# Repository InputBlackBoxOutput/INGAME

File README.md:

# INGAME

INGAME is a motion emulator with virtual reality features for playing first person
shooting/adventure games. Virtual reality (VR) is a simulated experience that can be similar to
or completely different from the real world. INGAME has been designed to provide the user
with the feeling of being 'IN-the-GAME'. INGAME is modular in nature and consists of the
following modules.

1. HID module
1. Controller module
1. Pedometer module
1. VR headset

The first three modules listed above have been explained in detail later in the document. The
VR headset provides split stereo video to the user. The following image shows the functional
block diagram of the INGAME system 

## Salient features
* Modular to support addons
* Tangle free gaming since the entire system is wireless
* Adaptable to any first person shooting/adventure game
* Minimal lag during gaming due to high-speed data transfer
* Power saving mode to make the battery last longer
* Product certifications: CE certified and ROHS compliant 

## HID module 

### Functions 
- Act as a wireless gateway between the modules worn by the user and the computer
- Connect with the computer via USB as an HID device
- Receive data wirelessly and then map the data to controls of the selected game and send appropriate key strokes to the computer
- Switch the game controls mapping depending on the user selected game
- Display a menu showing information about the system

## Controller module

### Functions
- Connect with the HID module wirelessly
- Send data associated with a button when a button is pressed
- Read IMU data, compute equivalent mouse movement and send the data to the HID module
- Calibrate the IMU device when the calibration button is pressed
- Monitor battery level and sound a buzzer when the battery is low
- Switch to power saving mode upon user inactivity
- [Optional] Control a vibration motor to simulate gunfire which increases in intensity per trigger button press

## Pedometer module

### Functions
- Connect with the HID module wirelessly
- Read accelerometer data, detect steps and send the data to the HID module
- Calibrate the IMU device when the calibration button is pressed
- Monitor battery level and sound a buzzer when the battery is low
- Switch to power saving mode upon user inactivity

## VR Headset
### Frame
|\#|Source|
|--|--|
|1|https://www.alibaba.com/product-detail/Vr-Helmet-SC-G07E-9-0_1600236677589.html|
||https://www.alibaba.com/product-detail/VR-G02ED-headset-version-Blu-ray_1600236686455.html|

### Display
|\#|Source|
|--|--|
|1|https://www.aliexpress.us/item/3256804913653723.html|
|2|https://www.alibaba.com/product-detail/Tft-Display-Driver-Board-VR-Headset_60669018564.html|

### Made with lots of ⏱️, 📚 and ☕ by InputBlackBoxOutput

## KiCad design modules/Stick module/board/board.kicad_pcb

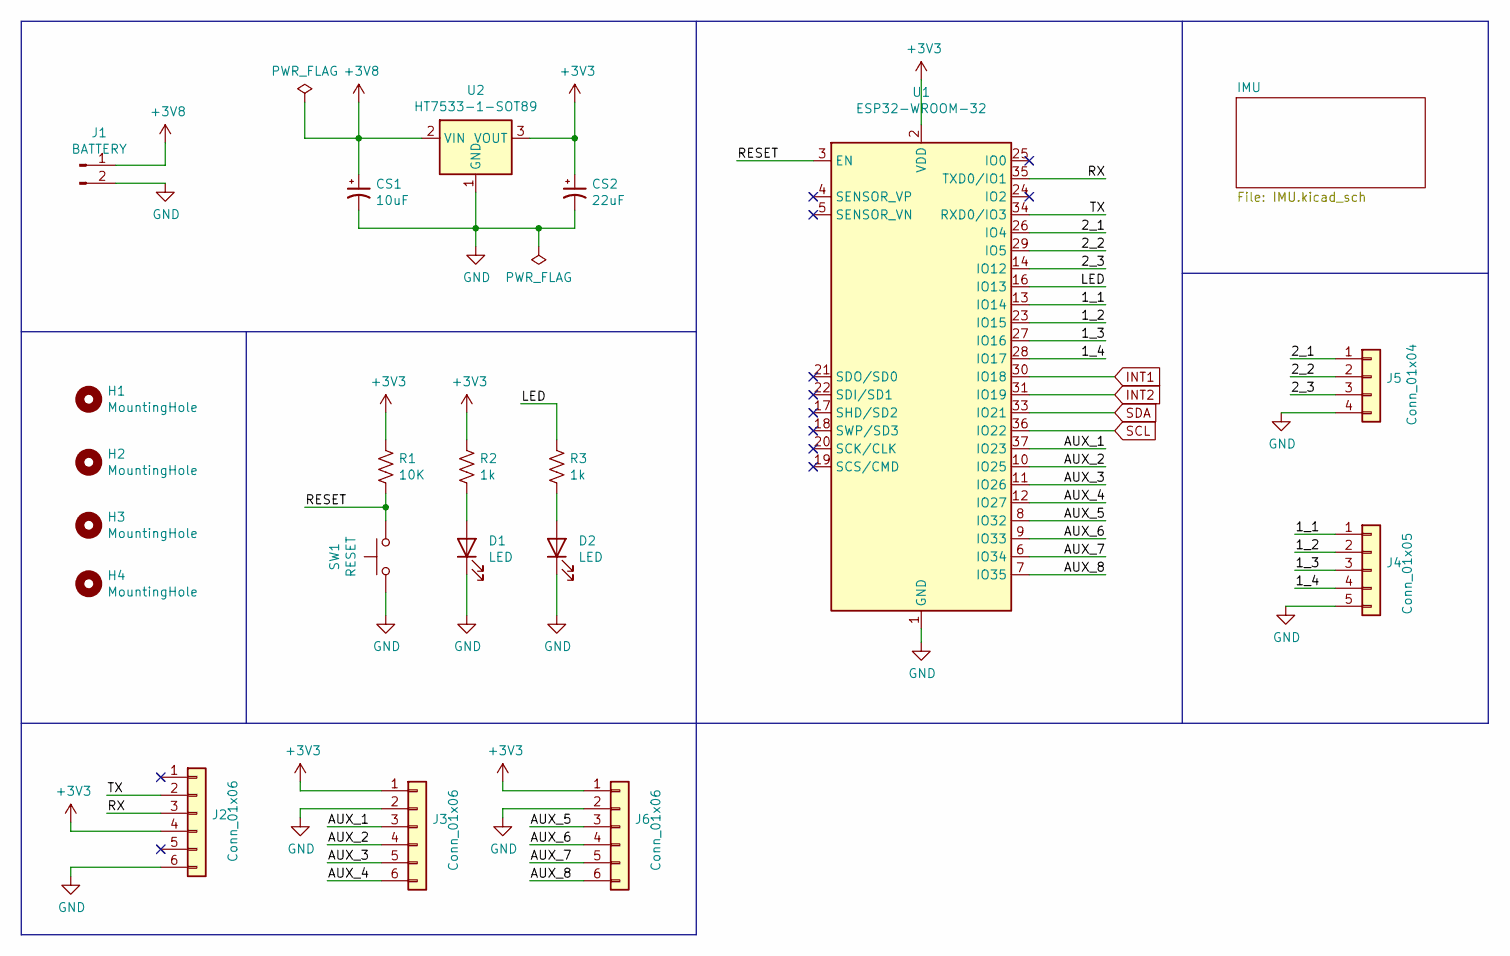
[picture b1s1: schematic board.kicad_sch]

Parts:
CS1: 10uF; C_0805_2012Metric_Pad1.18x1.45mm_HandSolder
CS2: 22uF; C_0805_2012Metric_Pad1.18x1.45mm_HandSolder
D1, D2: LED; LED_0805_2012Metric_Pad1.15x1.40mm_HandSolder
H1, H2, H3, H4: MountingHole; MountingHole_2.2mm_M2
J1: BATTERY; SolderWire_1x02_P2.00mm
J2, J3, J6: Conn_01x06; SolderWire_1x06_P2.54mm
J4: Conn_01x05; SolderWire_1x05_P2.54mm
J5: Conn_01x04; SolderWire_1x04_P2.54mm
R1: 10K; R_0805_2012Metric_Pad1.20x1.40mm_HandSolder
R2, R3: 1k; R_0805_2012Metric_Pad1.20x1.40mm_HandSolder
SW1: RESET; SW_SPST_B3U-1000P
U1: ESP32-WROOM-32
U2: HT7533-1-SOT89; SOT-89-3

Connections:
+3V3: CS2.1, J2.4, J3.1, J6.1, R1.1, R2.1, U1.2 (VDD), U2.3 (VOUT); also elsewhere on the board
+3V8: CS1.1, J1.1, U2.2 (VIN)
/1_1: J4.1, U1.13 (IO14)
/1_2: J4.2, U1.23 (IO15)
/1_3: J4.3, U1.27 (IO16)
/1_4: J4.4, U1.28 (IO17)
/2_1: J5.1, U1.26 (IO4)
/2_2: J5.2, U1.29 (IO5)
/2_3: J5.3, U1.14 (IO12)
/AUX_1: J3.3, U1.37 (IO23)
/AUX_2: J3.4, U1.10 (IO25)
/AUX_3: J3.5, U1.11 (IO26)
/AUX_4: J3.6, U1.12 (IO27)
/AUX_5: J6.3, U1.8 (IO32)
/AUX_6: J6.4, U1.9 (IO33)
/AUX_7: J6.5, U1.6 (IO34)
/AUX_8: J6.6, U1.7 (IO35)
/LED: R3.1, U1.16 (IO13)
/RESET: R1.2, SW1.2, U1.3 (EN)
/RX: J2.3, U1.35 (TXD0/IO1)
/TX: J2.2, U1.34 (RXD0/IO3)
GND: CS1.2, CS2.2, D1.1 (K), D2.1 (K), J1.2, J2.6, J3.2, J4.5, J5.4, J6.2, SW1.1, U1.1 (GND), U1.15 (GND), U1.38 (GND), U1.39 (GND), U2.1 (GND); also elsewhere on the board
INT1: U1.30 (IO18); also elsewhere on the board
INT2: U1.31 (IO19); also elsewhere on the board
unnamed: D1.2 (A), R2.2
unnamed: D2.2 (A), R3.2
SCL: U1.36 (IO22); also elsewhere on the board
SDA: U1.33 (IO21); also elsewhere on the board

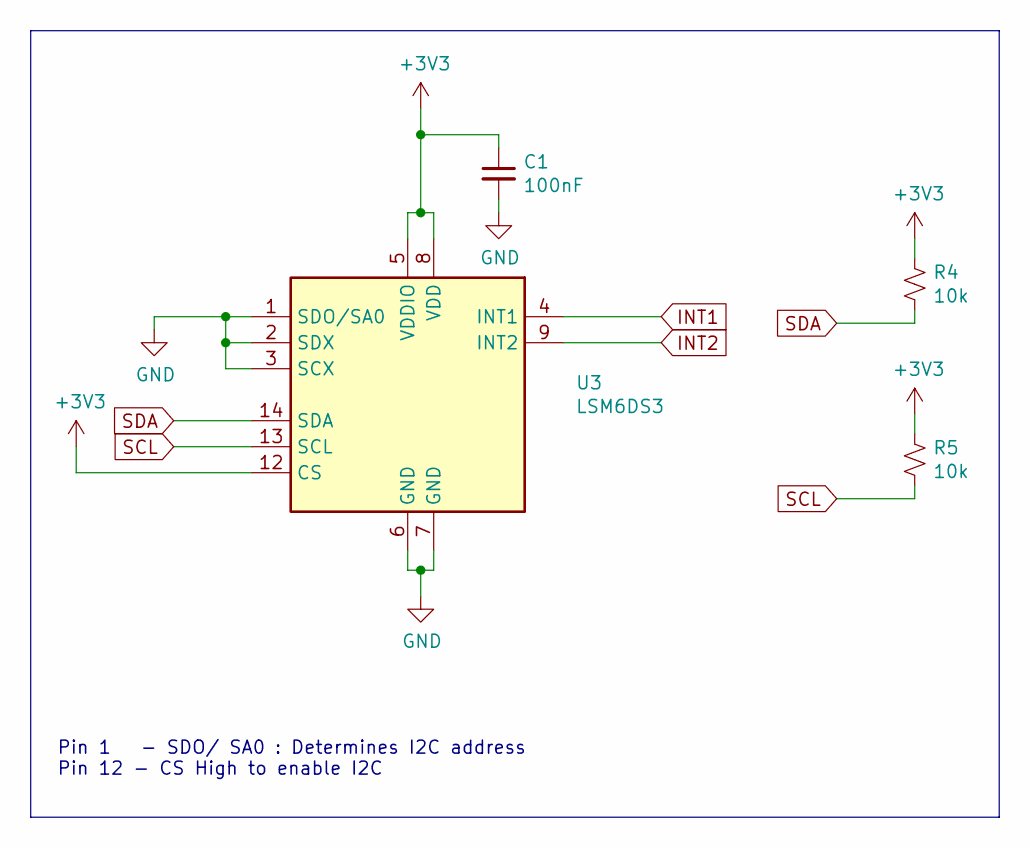
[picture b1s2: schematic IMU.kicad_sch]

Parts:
C1: 100nF; C_0805_2012Metric_Pad1.18x1.45mm_HandSolder
R4, R5: 10k; R_0805_2012Metric_Pad1.20x1.40mm_HandSolder
U3: LSM6DS3; LGA-14_3x2.5mm_P0.5mm_LayoutBorder3x4y

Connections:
+3V3: C1.1, R4.1, R5.1, U3.5 (VDDIO), U3.8 (VDD), U3.12 (CS); also elsewhere on the board
GND: C1.2, U3.1 (SDO/SA0), U3.2 (SDX), U3.3 (SCX), U3.6 (GND), U3.7 (GND); also elsewhere on the board
INT1: U3.4 (INT1); also elsewhere on the board
INT2: U3.9 (INT2); also elsewhere on the board
SCL: R5.2, U3.13 (SCL); also elsewhere on the board
SDA: R4.2, U3.14 (SDA); also elsewhere on the board

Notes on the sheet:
Pin 1 - SDO/ SA0 : Determines I2C address Pin 12 - CS High to enable I2C

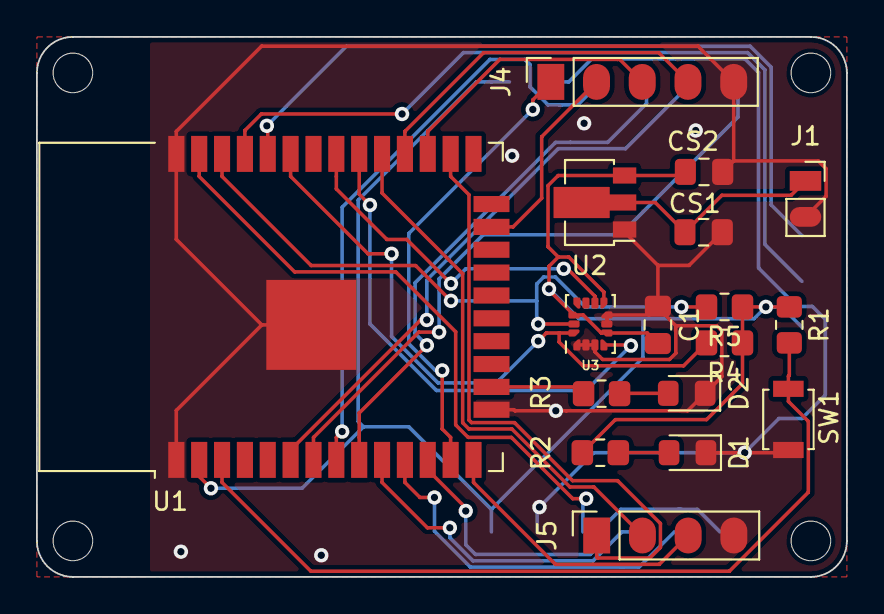
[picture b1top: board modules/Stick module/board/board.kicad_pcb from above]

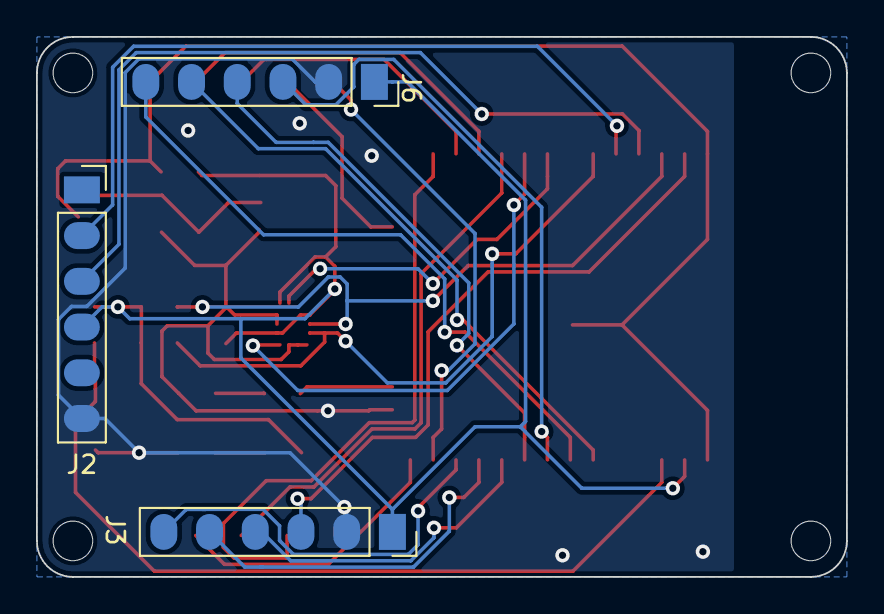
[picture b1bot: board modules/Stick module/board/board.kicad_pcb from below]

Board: 2 copper layers, 45.0 x 30.0 mm, 24 parts (3 on the bottom side), 28 nets.

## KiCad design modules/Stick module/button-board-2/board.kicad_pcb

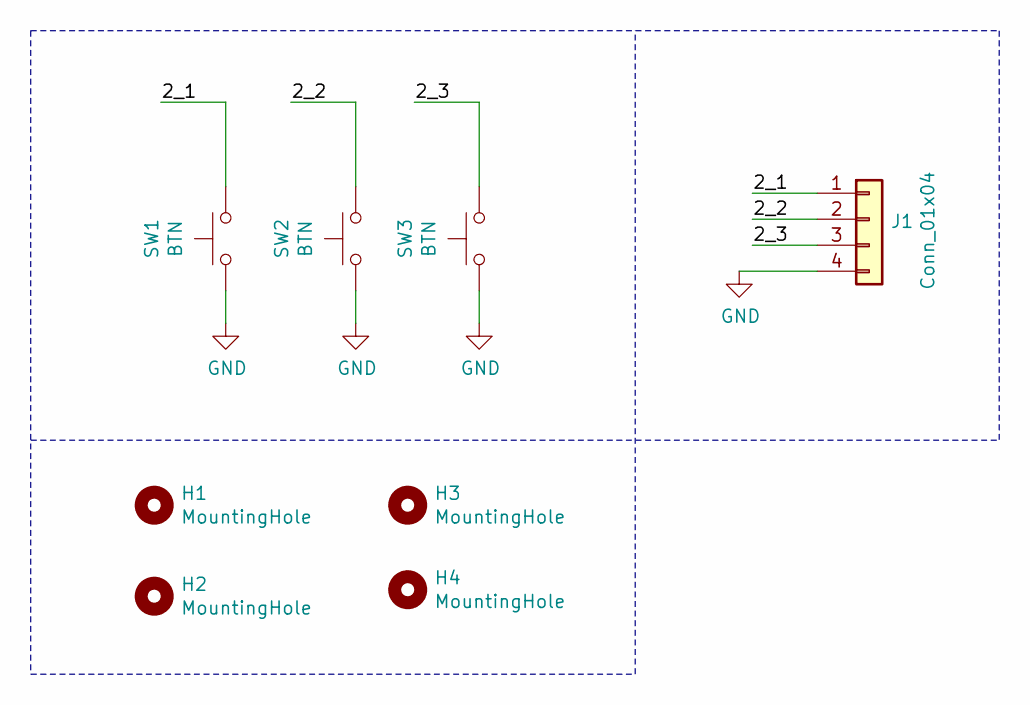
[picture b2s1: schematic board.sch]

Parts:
H1, H2, H3, H4: MountingHole; MountingHole_2.2mm_M2
J1: Conn_01x04; SolderWire_1x04_P2.54mm
SW1, SW2, SW3: BTN; SW_SPST_Omron_B3FS-100xP

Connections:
/2_1: J1.1, SW1.2
/2_2: J1.2, SW2.2
/2_3: J1.3, SW3.2
GND: J1.4, SW1.1, SW2.1, SW3.1

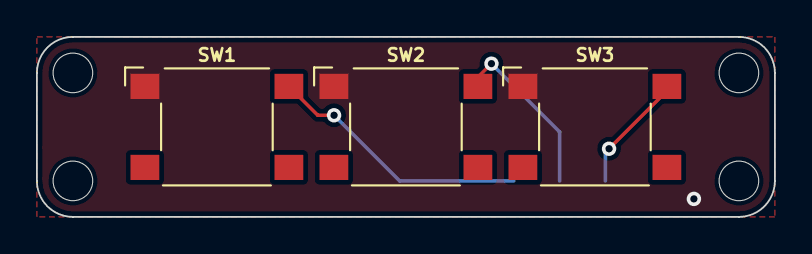
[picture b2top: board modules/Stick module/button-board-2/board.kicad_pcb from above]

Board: 2 copper layers, 41.0 x 10.0 mm, 8 parts (1 on the bottom side), 4 nets.

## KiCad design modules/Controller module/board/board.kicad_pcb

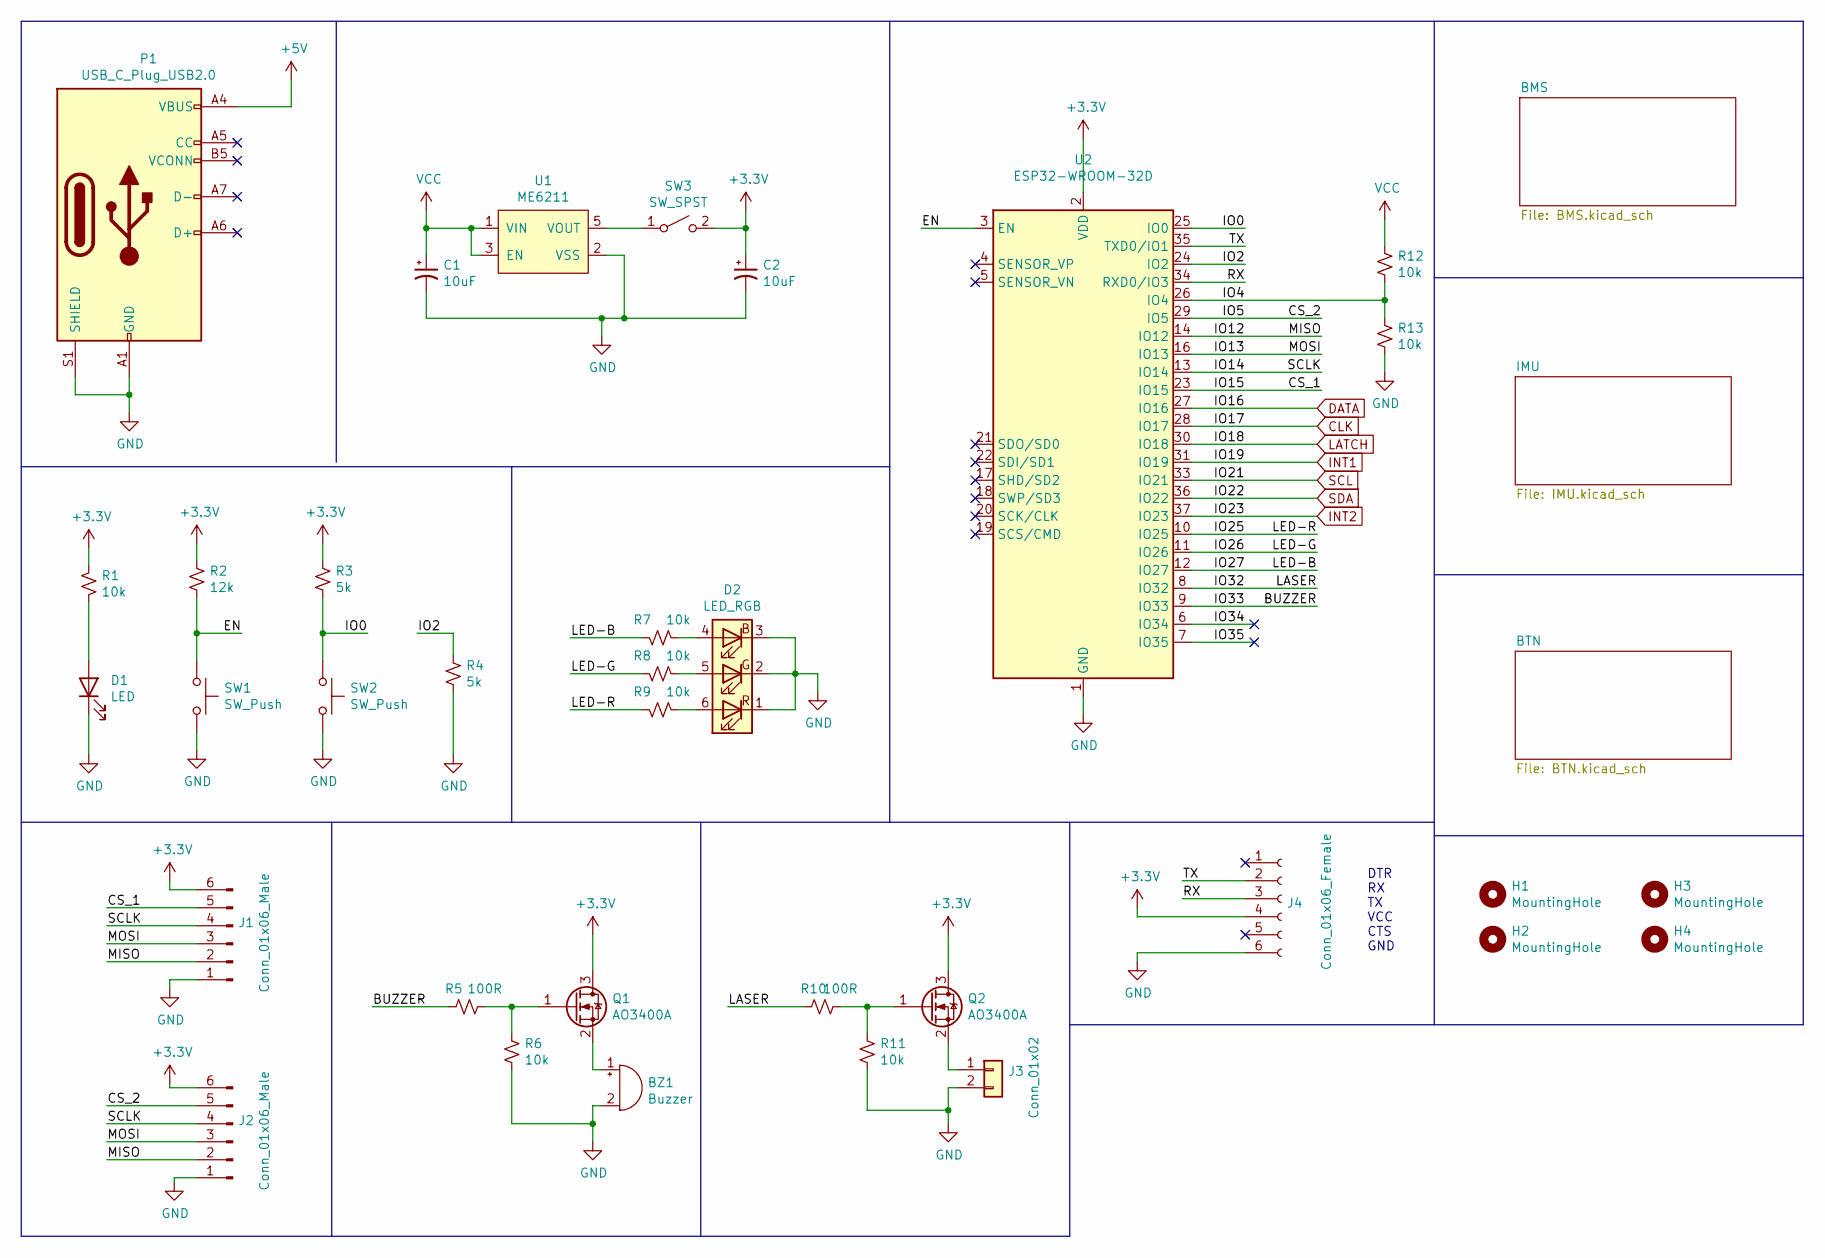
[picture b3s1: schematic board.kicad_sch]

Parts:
BZ1: Buzzer; Buzzer_Murata_PKMCS0909E4000-R1
C1, C2: 10uF; C_0805_2012Metric_Pad1.18x1.45mm_HandSolder
D1: LED; LED_0805_2012Metric_Pad1.15x1.40mm_HandSolder
D2: LED_RGB; LED_RGB_5050-6
H1, H2, H3, H4: MountingHole; MountingHole_2.2mm_M2
J1, J2: Conn_01x06_Male; SolderWire_1x06_P2.54mm
J3: Conn_01x02; SolderWire_1x02_P2.00mm
J4: Conn_01x06_Female; SolderWire_1x06_P2.54mm
P1: USB_C_Plug_USB2.0; GCT_USB4151-GF-C_REVA
Q1, Q2: AO3400A; SOT-23
R1, R6, R7, R8, R9, R11, R12, R13: 10k; R_0805_2012Metric_Pad1.20x1.40mm_HandSolder
R2: 12k; R_0805_2012Metric_Pad1.20x1.40mm_HandSolder
R3, R4: 5k; R_0805_2012Metric_Pad1.20x1.40mm_HandSolder
R5, R10: 100R; R_0805_2012Metric_Pad1.20x1.40mm_HandSolder
SW1, SW2: SW_Push; SW_SPST_B3U-1000P
SW3: SW_SPST; SolderWire_1x02_P2.00mm
U1: ME6211; SOT-23-5_HandSoldering
U2: ESP32-WROOM-32D; ESP32-WROOM-32

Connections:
+5V: P1.A4 (VBUS), P1.A9 (VBUS), P1.B4 (VBUS), P1.B9 (VBUS); also elsewhere on the board
/BUZZER: R5.2, U2.9 (IO33)
/CS_1: J1.5, U2.23 (IO15)
/CS_2: J2.5, U2.29 (IO5)
/EN: R2.2, SW1.1, U2.3 (EN)
/IO0: R3.2, SW2.1, U2.25 (IO0)
/IO2: R4.1, U2.24 (IO2)
/IO4: R12.2, R13.1, U2.26 (IO4)
/IO12: J1.2, J2.2, U2.14 (IO12)
/IO13: J1.3, J2.3, U2.16 (IO13)
/IO14: J1.4, J2.4, U2.13 (IO14)
/IO25: R9.1, U2.10 (IO25)
/IO26: R8.1, U2.11 (IO26)
/IO27: R7.1, U2.12 (IO27)
/IO32: R10.2, U2.8 (IO32)
/RX: J4.3, U2.34 (RXD0/IO3)
/TX: J4.2, U2.35 (TXD0/IO1)
CLK: U2.28 (IO17); also elsewhere on the board
DATA: U2.27 (IO16); also elsewhere on the board
GND: BZ1.2 (+), C1.2, C2.2, D1.1 (K), D2.1 (RK), D2.2 (GK), D2.3 (BK), J1.1, J2.1, J3.2, J4.6, P1.A1 (GND), P1.A12 (GND), P1.B1 (GND), P1.B12 (GND), P1.S1 (SHIELD), R4.2, R6.2, R11.2, R13.2, SW1.2, SW2.2, U1.2 (VSS), U2.1 (GND), U2.15 (GND), U2.38 (GND), U2.39 (GND); also elsewhere on the board
INT1: U2.31 (IO19); also elsewhere on the board
INT2: U2.37 (IO23); also elsewhere on the board
LATCH: U2.30 (IO18); also elsewhere on the board
unnamed: BZ1.1 (-), Q1.2 (S)
unnamed: D1.2 (A), R1.2
unnamed: D2.4 (BA), R7.2
unnamed: D2.5 (GA), R8.2
unnamed: D2.6 (RA), R9.2
unnamed: J3.1, Q2.2 (S)
unnamed: Q1.1 (G), R5.1, R6.1
unnamed: Q2.1 (G), R10.1, R11.1
unnamed: SW3.1 (A), U1.5 (VOUT)
SCL: U2.33 (IO21); also elsewhere on the board
SDA: U2.36 (IO22); also elsewhere on the board
VCC: C1.1, R12.1, U1.1 (VIN), U1.3 (EN); also elsewhere on the board

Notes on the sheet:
DTR RX TX VCC CTS GND

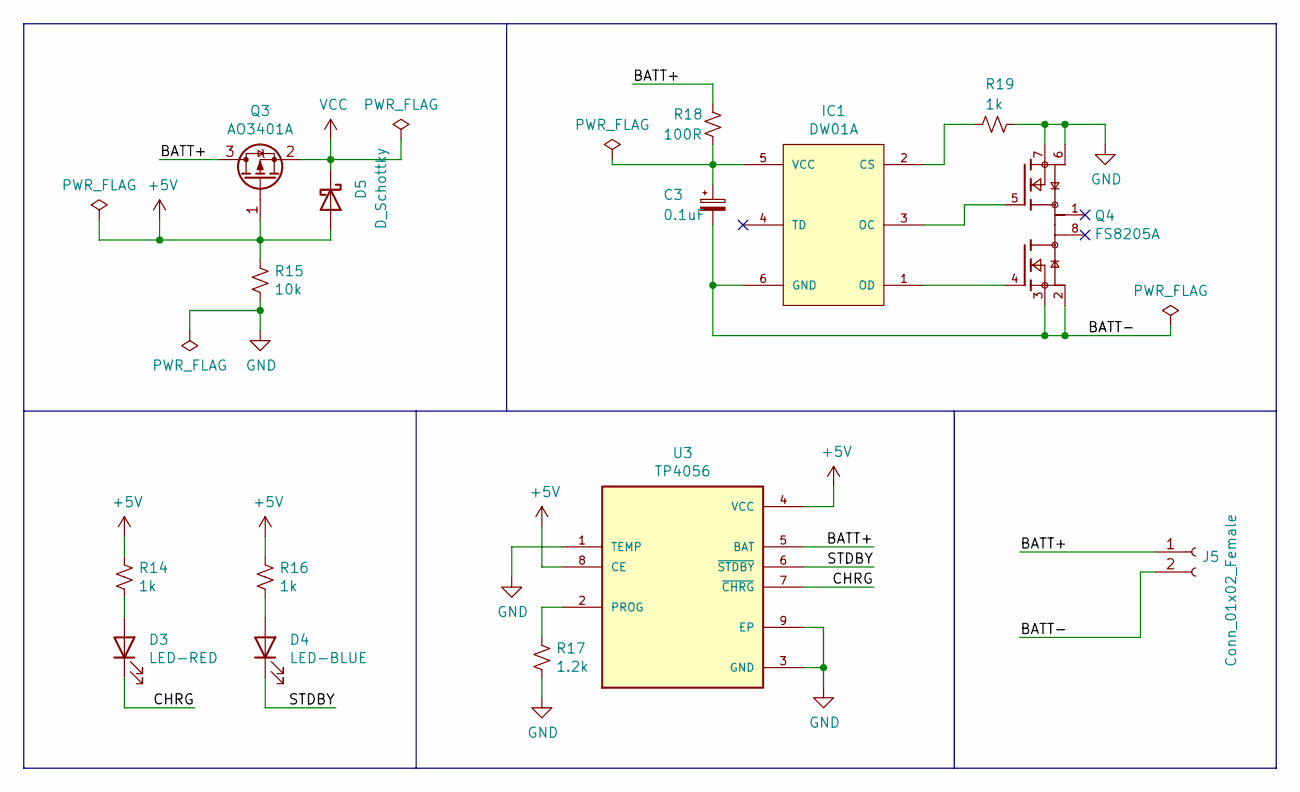
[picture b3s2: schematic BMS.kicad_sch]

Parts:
C3: 0.1uF; C_0805_2012Metric_Pad1.18x1.45mm_HandSolder
D3: LED-RED; LED_0805_2012Metric_Pad1.15x1.40mm_HandSolder
D4: LED-BLUE; LED_0805_2012Metric_Pad1.15x1.40mm_HandSolder
D5: D_Schottky; D_SMA
IC1: DW01A; SOT-23-6_Handsoldering; MPN DW01A; LCSC C351410
J5: Conn_01x02_Female; SolderWire_1x02_P2.00mm
Q3: AO3401A; SOT-23
Q4: FS8205A; SOP65P640X120-8N; PARTREV 1.7
R14, R16, R19: 1k; R_0805_2012Metric_Pad1.20x1.40mm_HandSolder
R15: 10k; R_0805_2012Metric_Pad1.20x1.40mm_HandSolder
R17: 1.2k; R_0805_2012Metric_Pad1.20x1.40mm_HandSolder
R18: 100R; R_0805_2012Metric_Pad1.20x1.40mm_HandSolder
U3: TP4056; SOP127P600X175-9N

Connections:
+5V: D5.2 (A), Q3.1 (G), R14.1, R15.1, R16.1, U3.4 (VCC), U3.8 (CE); also elsewhere on the board
/BMS/BATT+: J5.1, Q3.3 (D), R18.1, U3.5 (BAT)
/BMS/BATT-: C3.2, IC1.6 (GND), J5.2, Q4.2, Q4.3
/BMS/CHRG: D3.1 (K), U3.7 (~CHRG)
/BMS/STDBY: D4.1 (K), U3.6 (~STDBY)
GND: Q4.6, Q4.7, R15.2, R17.2, R19.1, U3.1 (TEMP), U3.3 (GND), U3.9 (EP); also elsewhere on the board
unnamed: C3.1, IC1.5 (VCC), R18.2
unnamed: D3.2 (A), R14.2
unnamed: D4.2 (A), R16.2
unnamed: IC1.1 (OD), Q4.4
unnamed: IC1.2 (CS), R19.2
unnamed: IC1.3 (OC), Q4.5
unnamed: R17.1, U3.2 (PROG)
VCC: D5.1 (K), Q3.2 (S); also elsewhere on the board

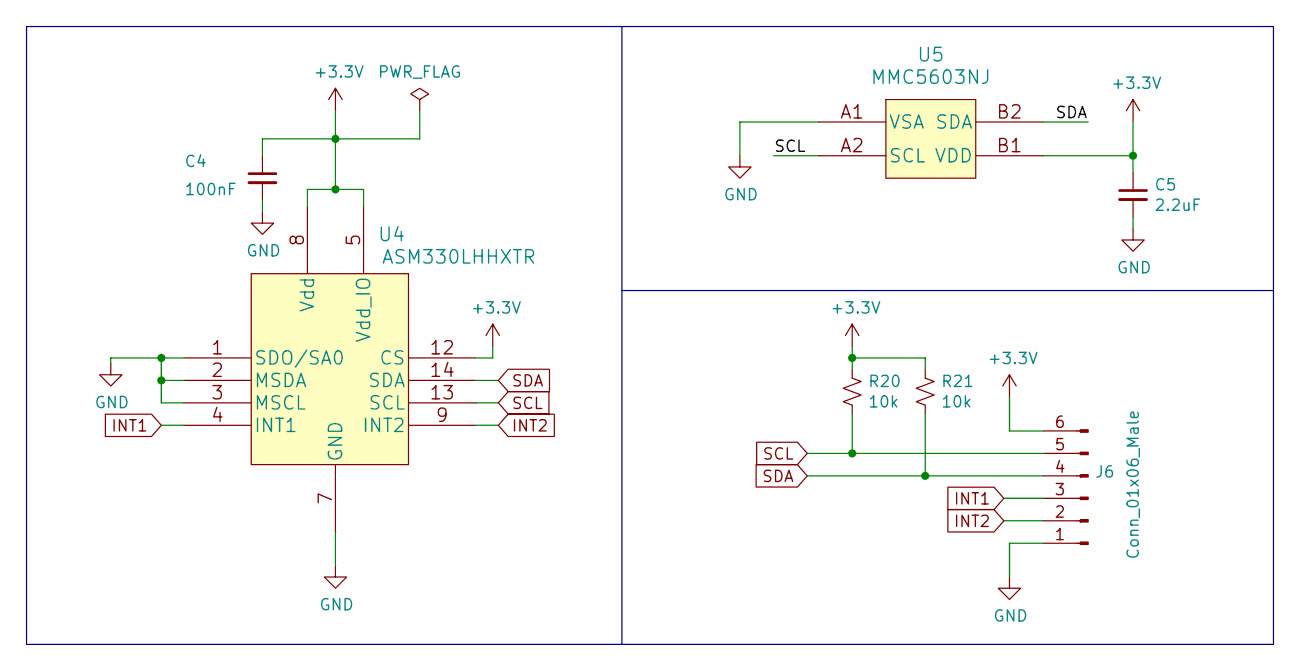
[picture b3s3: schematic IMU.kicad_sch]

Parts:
C4: 100nF; C_0603_1608Metric_Pad1.08x0.95mm_HandSolder
C5: 2.2uF; C_0603_1608Metric_Pad1.08x0.95mm_HandSolder
J6: Conn_01x06_Male; SolderWire_1x06_P2.54mm
R20, R21: 10k; R_0603_1608Metric_Pad0.98x0.95mm_HandSolder
U4: ASM330LHHXTR
U5: MMC5603NJ

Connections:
GND: C4.2, C5.2, J6.1, U4.1 (SDO/SA0), U4.2 (MSDA), U4.3 (MSCL), U4.7 (GND), U5.A1 (VSA); also elsewhere on the board
INT1: J6.3, U4.4 (INT1); also elsewhere on the board
INT2: J6.2, U4.9 (INT2); also elsewhere on the board
SCL: J6.5, R20.2, U4.13 (SCL), U5.A2 (SCL); also elsewhere on the board
SDA: J6.4, R21.2, U4.14 (SDA), U5.B2 (SDA); also elsewhere on the board

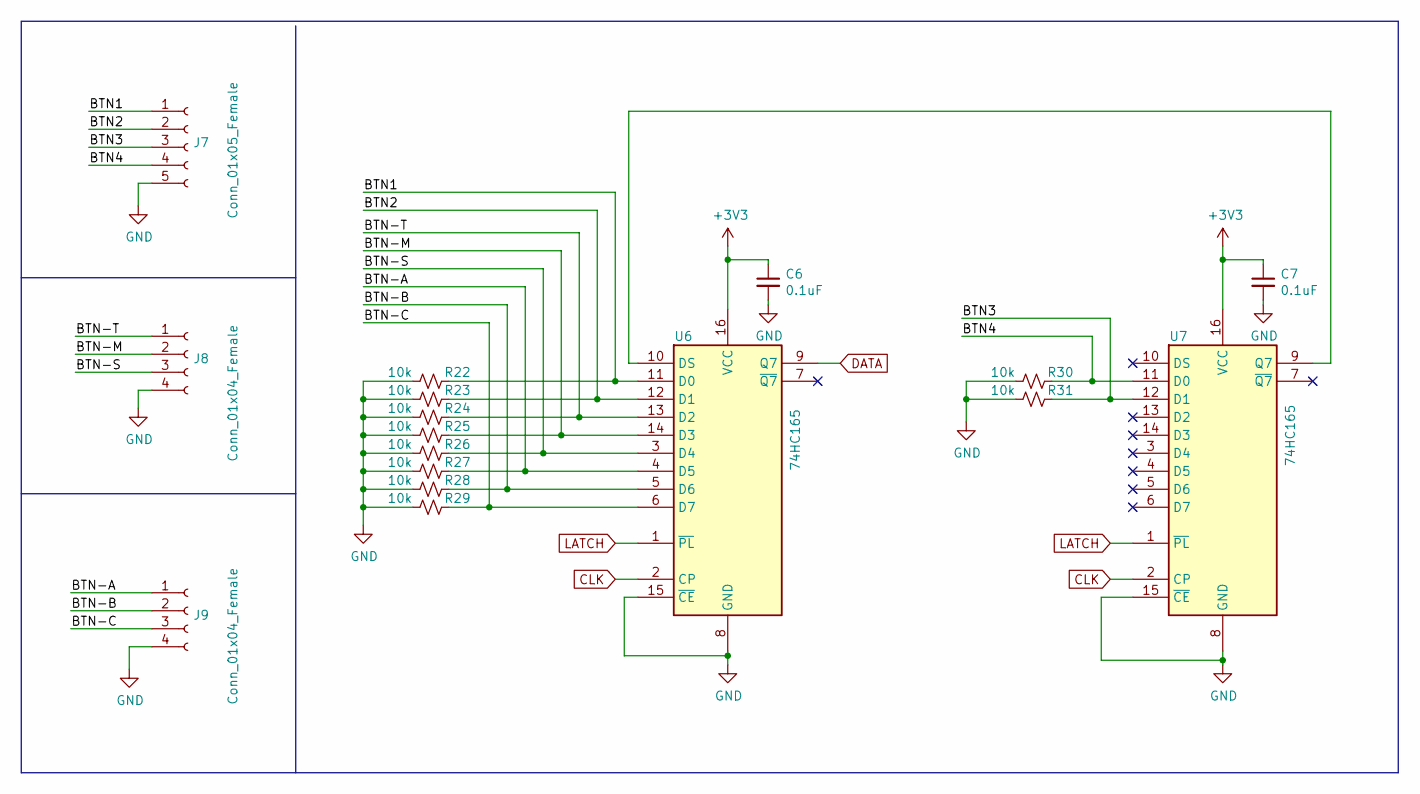
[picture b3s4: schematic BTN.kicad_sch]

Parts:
C6, C7: 0.1uF; C_0603_1608Metric_Pad1.08x0.95mm_HandSolder
J7: Conn_01x05_Female; SolderWire_1x05_P2.00mm
J8, J9: Conn_01x04_Female; SolderWire_1x04_P2.00mm
R22, R23, R24, R25, R26, R27, R28, R29, R30, R31: 10k; R_0805_2012Metric_Pad1.20x1.40mm_HandSolder
U6, U7: 74HC165; TSSOP-16_4.4x5mm_P0.65mm

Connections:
/BTN/BTN1: J7.1, R22.2, U6.11 (D0)
/BTN/BTN2: J7.2, R23.2, U6.12 (D1)
/BTN/BTN3: J7.3, R31.2, U7.12 (D1)
/BTN/BTN4: J7.4, R30.2, U7.11 (D0)
/BTN/BTN-A: J9.1, R27.2, U6.4 (D5)
/BTN/BTN-B: J9.2, R28.2, U6.5 (D6)
/BTN/BTN-C: J9.3, R29.2, U6.6 (D7)
/BTN/BTN-M: J8.2, R25.2, U6.14 (D3)
/BTN/BTN-S: J8.3, R26.2, U6.3 (D4)
/BTN/BTN-T: J8.1, R24.2, U6.13 (D2)
CLK: U6.2 (CP), U7.2 (CP); also elsewhere on the board
DATA: U6.9 (Q7); also elsewhere on the board
GND: C6.2, C7.2, J7.5, J8.4, J9.4, R22.1, R23.1, R24.1, R25.1, R26.1, R27.1, R28.1, R29.1, R30.1, R31.1, U6.8 (GND), U6.15 (~CE), U7.8 (GND), U7.15 (~CE); also elsewhere on the board
LATCH: U6.1 (~PL), U7.1 (~PL); also elsewhere on the board
unnamed: U6.10 (DS), U7.9 (Q7)

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
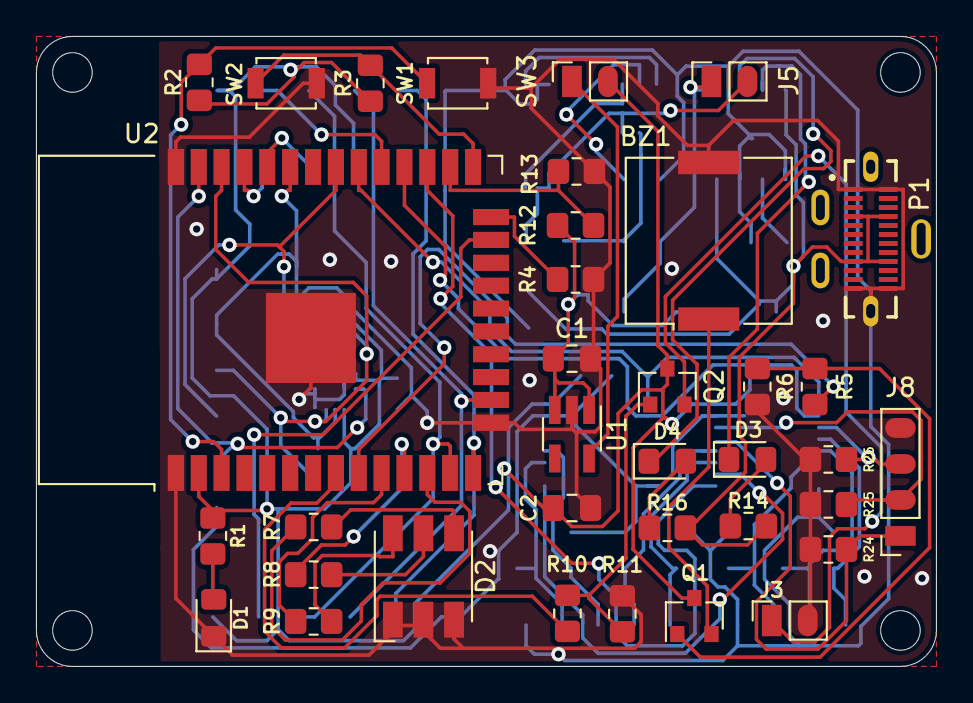
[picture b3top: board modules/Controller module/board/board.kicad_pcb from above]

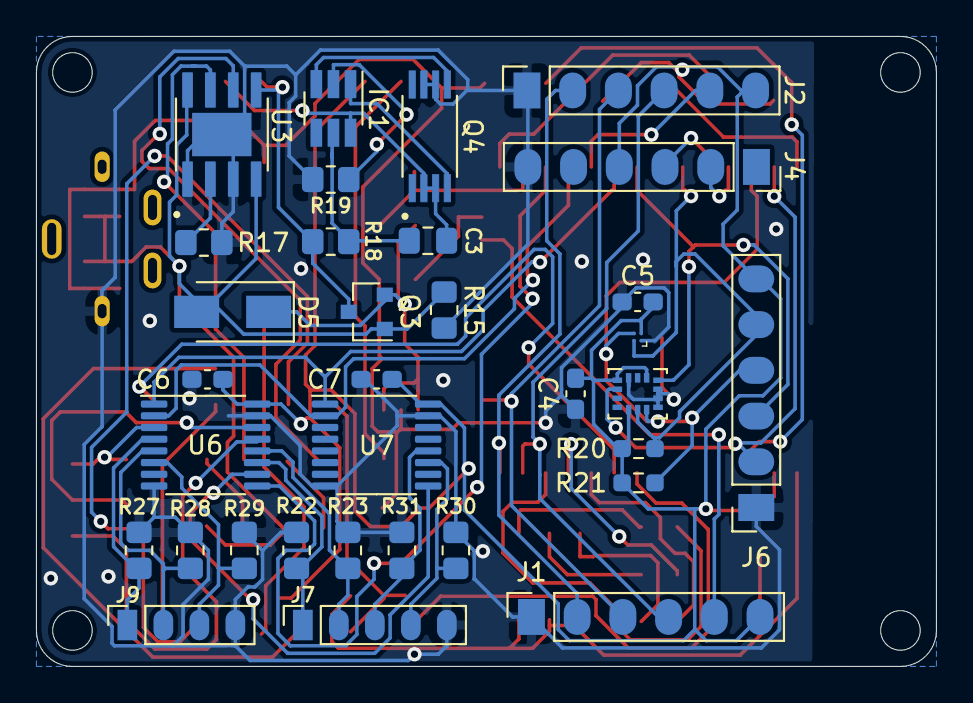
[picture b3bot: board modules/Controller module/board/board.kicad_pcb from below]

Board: 2 copper layers, 50.0 x 35.0 mm, 73 parts (33 on the bottom side), 58 nets.

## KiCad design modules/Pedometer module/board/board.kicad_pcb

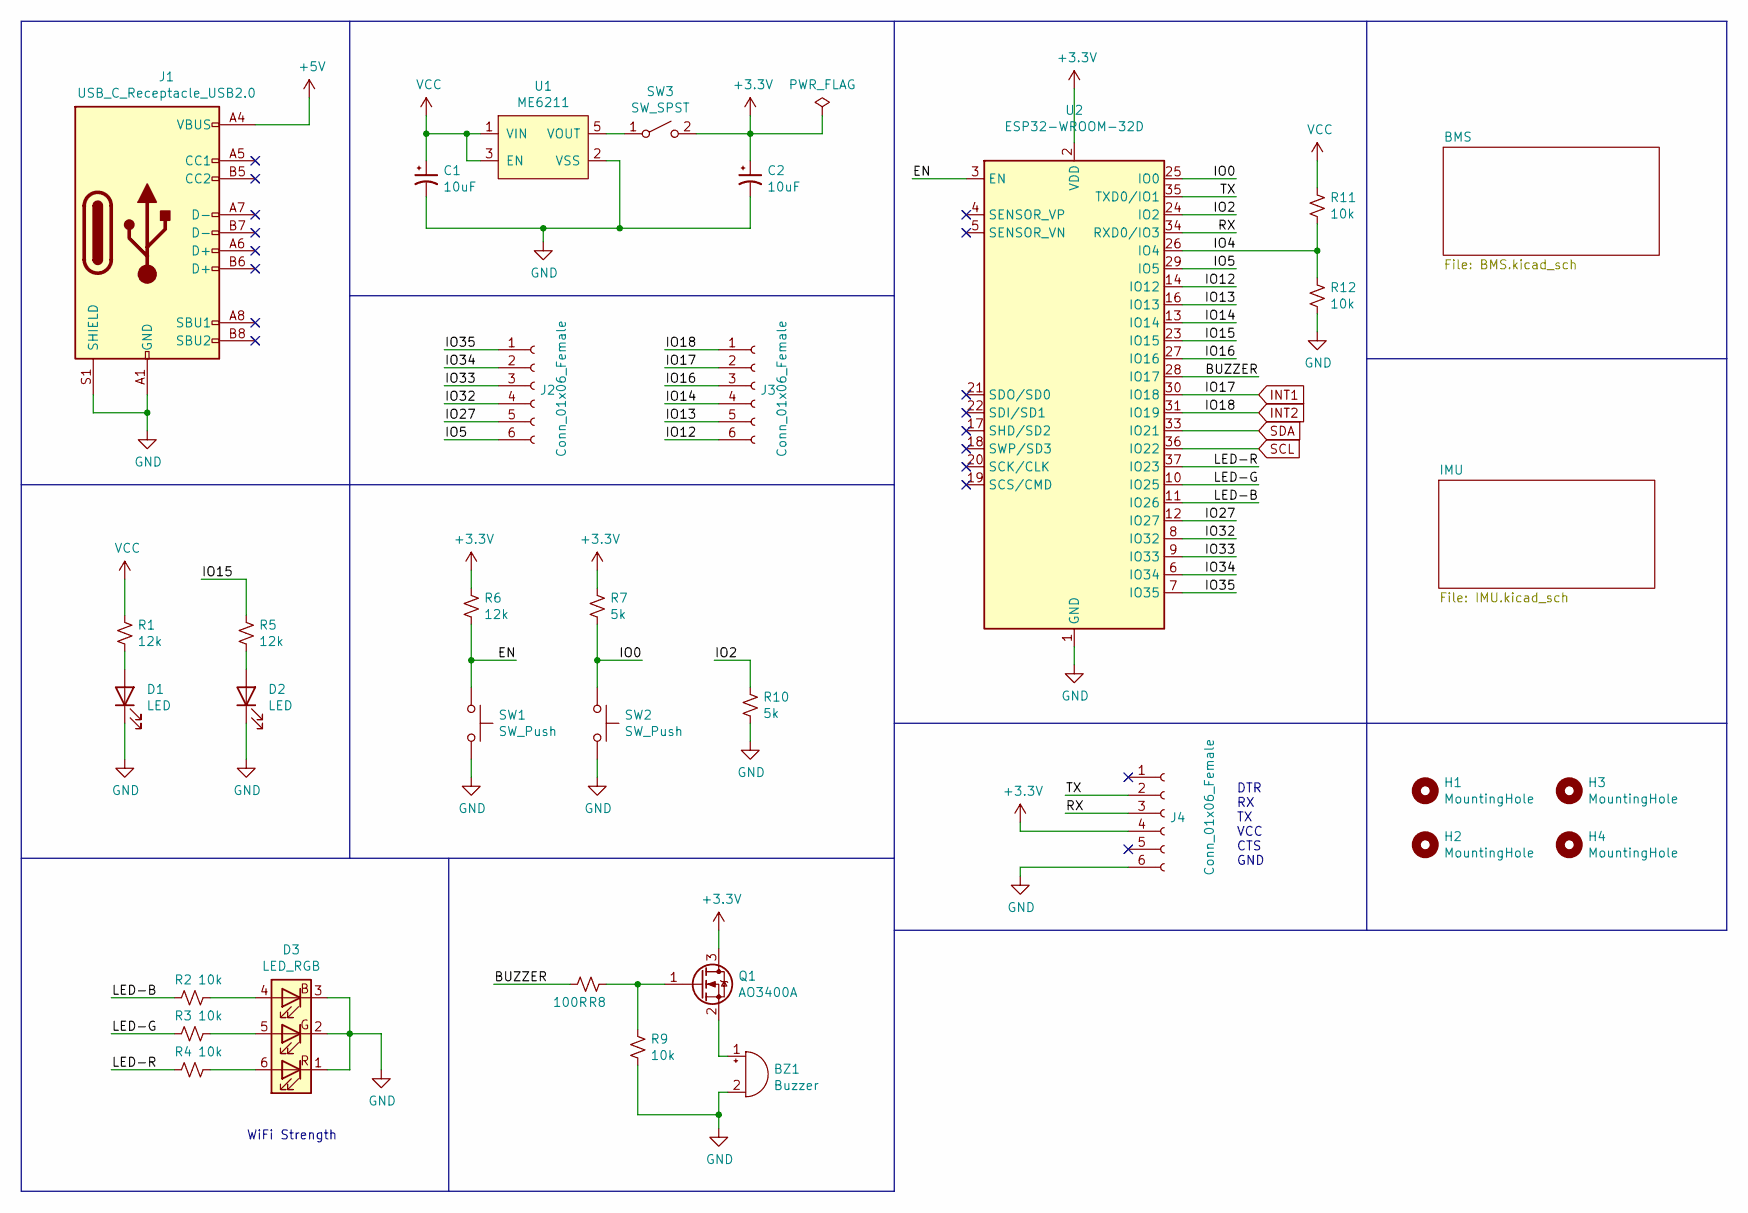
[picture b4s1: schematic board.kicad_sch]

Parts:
BZ1: Buzzer; Buzzer_Murata_PKMCS0909E4000-R1
C1, C2: 10uF; C_0805_2012Metric_Pad1.18x1.45mm_HandSolder
D1, D2: LED; LED_0805_2012Metric_Pad1.15x1.40mm_HandSolder
D3: LED_RGB; LED_RGB_5050-6
H1, H2: MountingHole; MountingHole_2.2mm_M2
H3, H4: MountingHole; MountingHole_2.5mm
J1: USB_C_Receptacle_USB2.0; USB_C_Receptacle_HRO_TYPE-C-31-M-12
J2, J3, J4: Conn_01x06_Female; SolderWire_1x06_P2.54mm
Q1: AO3400A; SOT-23
R1, R5, R6: 12k; R_0805_2012Metric_Pad1.20x1.40mm_HandSolder
R2, R3, R4, R9, R11, R12: 10k; R_0805_2012Metric_Pad1.20x1.40mm_HandSolder
R7, R10: 5k; R_0805_2012Metric_Pad1.20x1.40mm_HandSolder
R8: 100R; R_0805_2012Metric_Pad1.20x1.40mm_HandSolder
SW1, SW2: SW_Push; SW_SPST_B3U-1000P
SW3: SW_SPST; SW-SPDT-PCM12
U1: ME6211; SOT-23-5_HandSoldering
U2: ESP32-WROOM-32D; ESP32-WROOM-32

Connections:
+5V: J1.A4 (VBUS), J1.A9 (VBUS), J1.B4 (VBUS), J1.B9 (VBUS); also elsewhere on the board
/BUZZER: R8.1, U2.28 (IO17)
/EN: R6.2, SW1.1, U2.3 (EN)
/IO0: R7.2, SW2.1, U2.25 (IO0)
/IO2: R10.1, U2.24 (IO2)
/IO4: R11.2, R12.1, U2.26 (IO4)
/IO5: J2.6, U2.29 (IO5)
/IO12: J3.6, U2.14 (IO12)
/IO13: J3.5, U2.16 (IO13)
/IO14: J3.4, U2.13 (IO14)
/IO15: R5.1, U2.23 (IO15)
/IO16: J3.3, U2.27 (IO16)
/IO27: J2.5, U2.12 (IO27)
/IO32: J2.4, U2.8 (IO32)
/IO33: J2.3, U2.9 (IO33)
/IO34: J2.2, U2.6 (IO34)
/IO35: J2.1, U2.7 (IO35)
/LED-B: R2.2, U2.11 (IO26)
/LED-G: R3.2, U2.10 (IO25)
/LED-R: R4.2, U2.37 (IO23)
/RX: J4.3, U2.34 (RXD0/IO3)
/TX: J4.2, U2.35 (TXD0/IO1)
GND: BZ1.2 (+), C1.2, C2.2, D1.1 (K), D2.1 (K), D3.1 (RK), D3.2 (GK), D3.3 (BK), J1.A1 (GND), J1.A12 (GND), J1.B1 (GND), J1.B12 (GND), J1.S1 (SHIELD), J4.6, R9.2, R10.2, R12.2, SW1.2, SW2.2, U1.2 (VSS), U2.1 (GND), U2.15 (GND), U2.38 (GND), U2.39 (GND); also elsewhere on the board
INT1: J3.2, U2.30 (IO18); also elsewhere on the board
INT2: J3.1, U2.31 (IO19); also elsewhere on the board
unnamed: BZ1.1 (-), Q1.2 (S)
unnamed: D1.2 (A), R1.2
unnamed: D2.2 (A), R5.2
unnamed: D3.4 (BA), R2.1
unnamed: D3.5 (GA), R3.1
unnamed: D3.6 (RA), R4.1
unnamed: Q1.1 (G), R8.2, R9.1
unnamed: SW3.1 (A), U1.5 (VOUT)
SCL: U2.36 (IO22); also elsewhere on the board
SDA: U2.33 (IO21); also elsewhere on the board
VCC: C1.1, R1.1, R11.1, U1.1 (VIN), U1.3 (EN); also elsewhere on the board

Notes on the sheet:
WiFi Strength
DTR RX TX VCC CTS GND

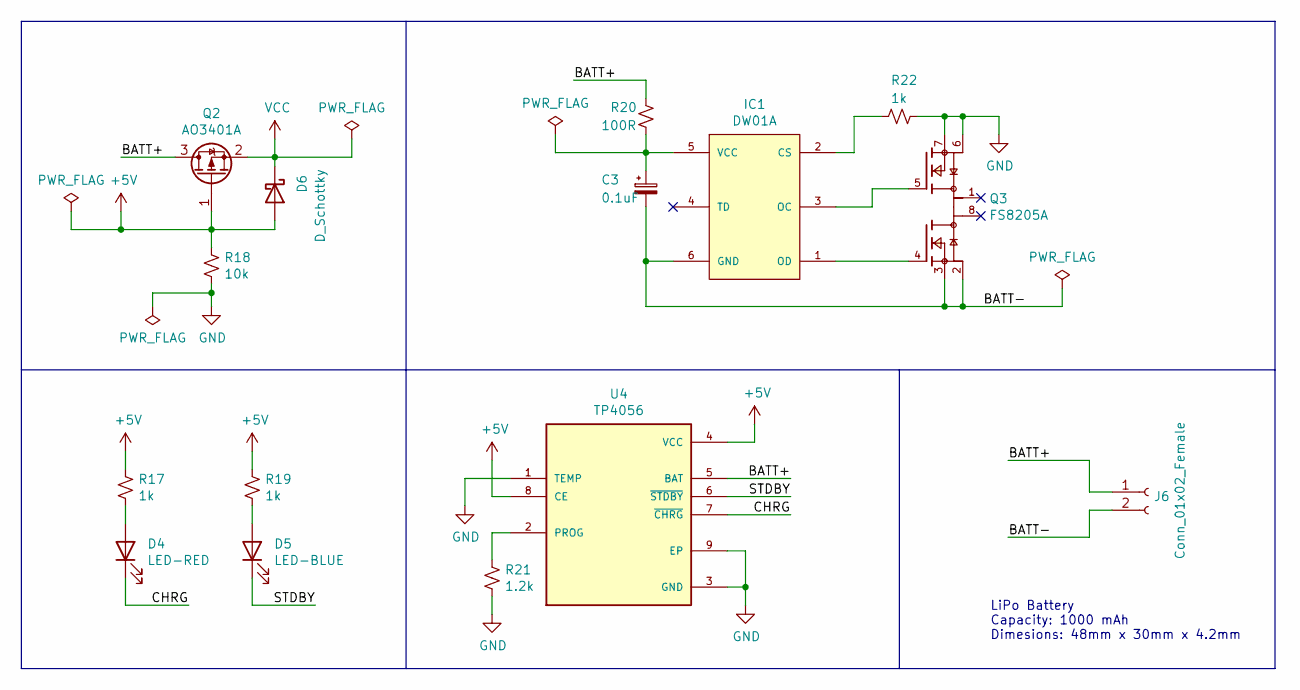
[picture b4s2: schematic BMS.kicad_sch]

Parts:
C3: 0.1uF; C_0805_2012Metric_Pad1.18x1.45mm_HandSolder
D4: LED-RED; LED_0805_2012Metric_Pad1.15x1.40mm_HandSolder
D5: LED-BLUE; LED_0805_2012Metric_Pad1.15x1.40mm_HandSolder
D6: D_Schottky; D_SMA
IC1: DW01A; SOT-23-6_Handsoldering; MPN DW01A; LCSC C351410
J6: Conn_01x02_Female; SolderWire_1x02_P2.00mm
Q2: AO3401A; SOT-23
Q3: FS8205A; SOP65P640X120-8N; PARTREV 1.7
R17, R19, R22: 1k; R_0805_2012Metric_Pad1.20x1.40mm_HandSolder
R18: 10k; R_0805_2012Metric_Pad1.20x1.40mm_HandSolder
R20: 100R; R_0805_2012Metric_Pad1.20x1.40mm_HandSolder
R21: 1.2k; R_0805_2012Metric_Pad1.20x1.40mm_HandSolder
U4: TP4056; SOP127P600X175-9N

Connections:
+5V: D6.2 (A), Q2.1 (G), R17.1, R18.1, R19.1, U4.4 (VCC), U4.8 (CE); also elsewhere on the board
/BMS/BATT+: J6.1, Q2.3 (D), R20.1, U4.5 (BAT)
/BMS/BATT-: C3.2, IC1.6 (GND), J6.2, Q3.2, Q3.3
/BMS/CHRG: D4.1 (K), U4.7 (~CHRG)
/BMS/STDBY: D5.1 (K), U4.6 (~STDBY)
GND: Q3.6, Q3.7, R18.2, R21.2, R22.1, U4.1 (TEMP), U4.3 (GND), U4.9 (EP); also elsewhere on the board
unnamed: C3.1, IC1.5 (VCC), R20.2
unnamed: D4.2 (A), R17.2
unnamed: D5.2 (A), R19.2
unnamed: IC1.1 (OD), Q3.4
unnamed: IC1.2 (CS), R22.2
unnamed: IC1.3 (OC), Q3.5
unnamed: R21.1, U4.2 (PROG)
VCC: D6.1 (K), Q2.2 (S); also elsewhere on the board

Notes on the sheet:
LiPo Battery Capacity: 1000 mAh Dimesions: 48mm x 30mm x 4.2mm
